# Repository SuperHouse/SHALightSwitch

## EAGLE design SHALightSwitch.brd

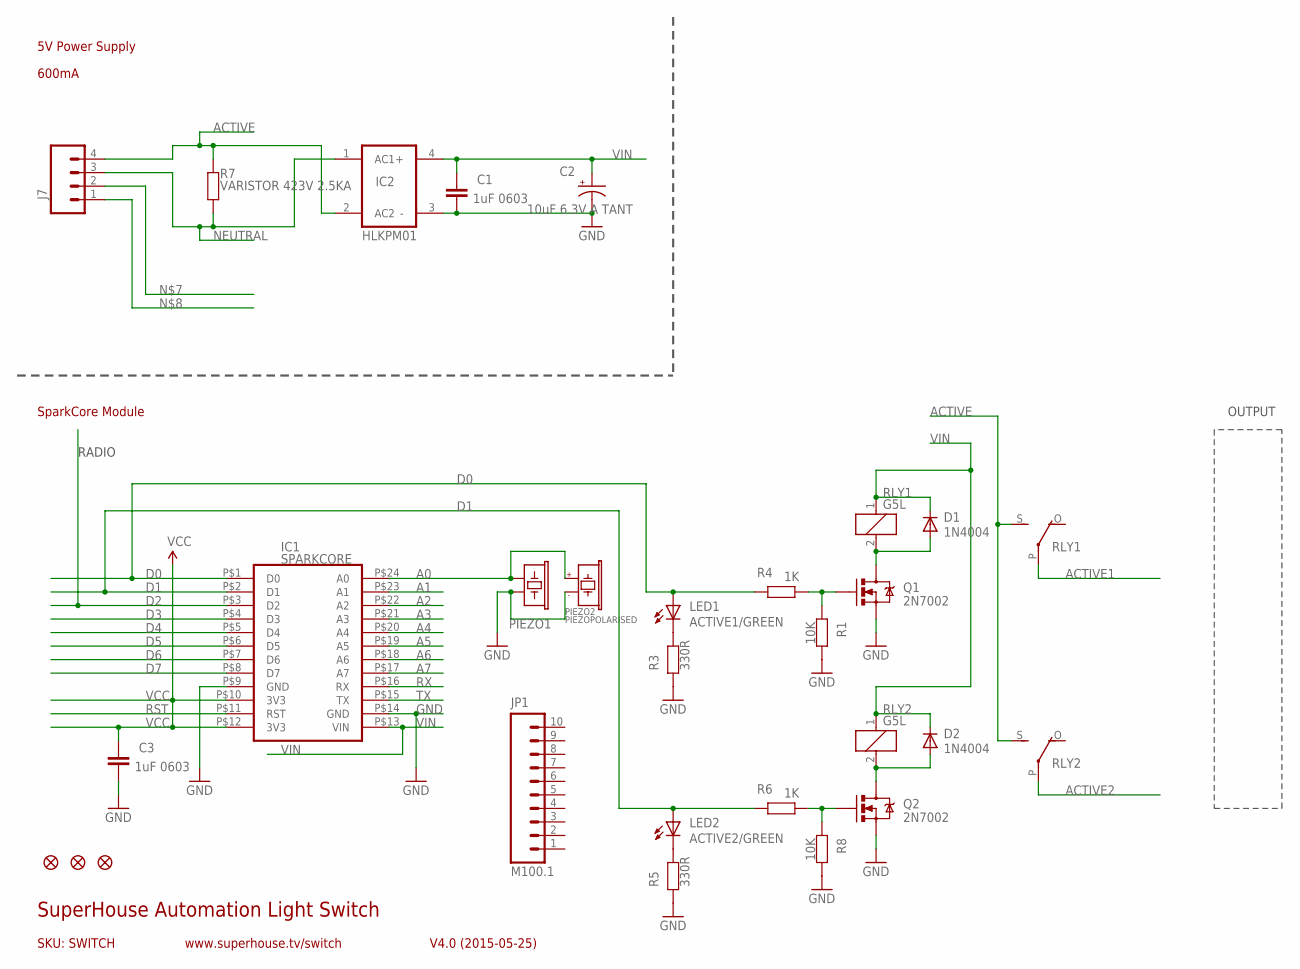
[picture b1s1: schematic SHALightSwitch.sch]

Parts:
C1, C3: 1uF 0603; 0603@1
C2: 10uF 6.3V A TANT; EIA3216
D1, D2: 1N4004; SMB-DIODE
FID1, FID2, FID3: FIDUCIAL1X2.5; FIDUCIAL-1X2.5
IC1: SPARKCORE
IC2: HLKPM01
J7: M04SCREW; SCREWTERMINAL-3.5MM-4
JP1: M100.1; 1X10
LED1: ACTIVE1/GREEN; LED-0603
LED2: ACTIVE2/GREEN; LED-0603
PIEZO1: BUZZERSMD12X12; BUZZER-12X12-SMT
PIEZO2: PIEZOPOLARISED; PIEZO12MMWIDEPOLARISED
Q1, Q2: 2N7002; SOT23-3
R1, R8: 10K; 0603
R3, R5: 330R; 0603
R4, R6: 1K; 0603
R7: VARISTOR 423V 2.5KA; AXIAL-0.3
RLY1, RLY2: G5L; G5LE

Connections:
A0: IC1.P$24 (A0), PIEZO1.1, PIEZO2.1 (+)
A1: IC1.P$23 (A1)
A2: IC1.P$22 (A2)
A3: IC1.P$21 (A3)
A4: IC1.P$20 (A4)
A5: IC1.P$19 (A5)
A6: IC1.P$18 (A6)
A7: IC1.P$17 (A7)
ACTIVE: IC2.2 (AC2), J7.4, R7.P$2 (2), RLY1.S, RLY2.S
ACTIVE1: RLY1.P
ACTIVE2: RLY2.P
D0: IC1.P$1 (D0), LED1.A, R4.2
D1: IC1.P$2 (D1), LED2.A, R6.2
D2: IC1.P$3 (D2)
D3: IC1.P$4 (D3)
D4: IC1.P$5 (D4)
D5: IC1.P$6 (D5)
D6: IC1.P$7 (D6)
D7: IC1.P$8 (D7)
GND: C1.2, C2.C (-), C3.2, IC1.P$9 (GND), IC1.P$14 (GND), IC2.3 (-), PIEZO1.2, PIEZO2.2 (-), Q1.2 (S), Q2.2 (S), R1.2, R3.1, R5.1, R8.2
unnamed: LED2.C, R5.2
unnamed: D2.A, Q2.3 (D), RLY2.2
unnamed: D1.A, Q1.3 (D), RLY1.2
unnamed: Q1.1 (G), R1.1, R4.1
unnamed: Q2.1 (G), R6.1, R8.1
unnamed: LED1.C, R3.2
NEUTRAL: IC2.1 (AC1), J7.3, R7.P$1 (1)
RST: IC1.P$11 (RST)
RX: IC1.P$16 (RX)
TX: IC1.P$15 (TX)
VCC: C3.1, IC1.P$10 (3V3), IC1.P$12 (3V3)
VIN: C1.1, C2.A (+), D1.C, D2.C, IC1.P$13 (VIN), IC2.4 (+), RLY1.1, RLY2.1

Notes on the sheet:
SKU: SWITCH
5V Power Supply
SparkCore Module
600mA
SuperHouse Automation Light Switch
V4.0 (2015-05-25)
www.superhouse.tv/switch
OUTPUT
RADIO

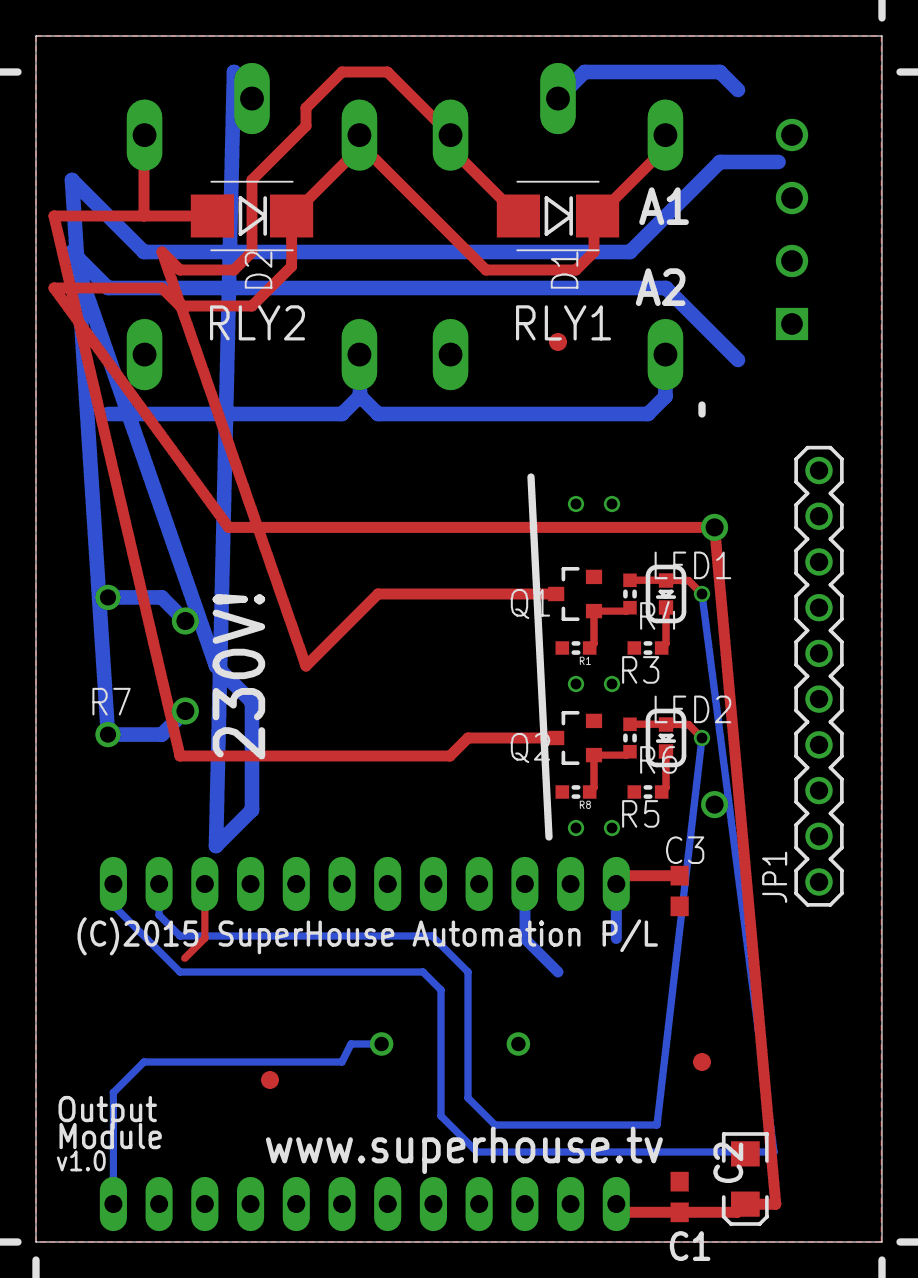
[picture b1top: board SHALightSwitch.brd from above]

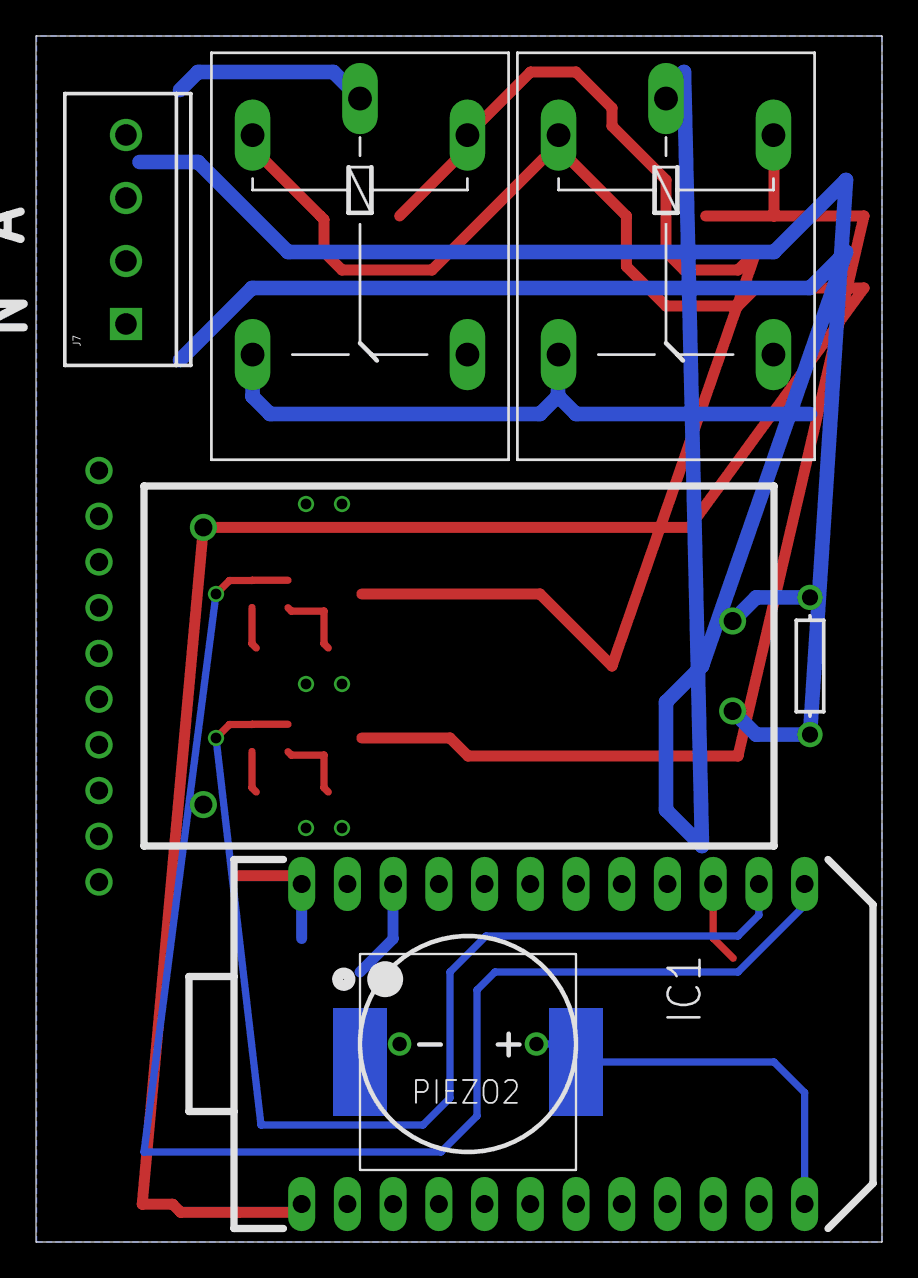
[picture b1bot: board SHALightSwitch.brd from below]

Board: 2 copper layers, 47.0 x 67.0 mm, 27 parts (8 on the bottom side), 14 nets.

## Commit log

2019-04-24 Import old project files

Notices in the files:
SHALightSwitch.brd:
(C)2015 SuperHouse Automation P/L
parts and their libraries:
freetronics-original: Licensing: CC v3.0 Share-Alike You are welcome to use this library for commercial purposes.
